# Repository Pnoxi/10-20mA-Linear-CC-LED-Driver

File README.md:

# 10-20mA-Linear-CC-LED-Driver

Documentation
--------------------

https://hackaday.io/project/164472-small-constant-current-linear-1020ma-driver

Donate
--------------------

Do you like my work? [Let me know about it and support my other projects!](https://www.patreon.com/pnoxi)

Or just drink beer on my honor :wink:

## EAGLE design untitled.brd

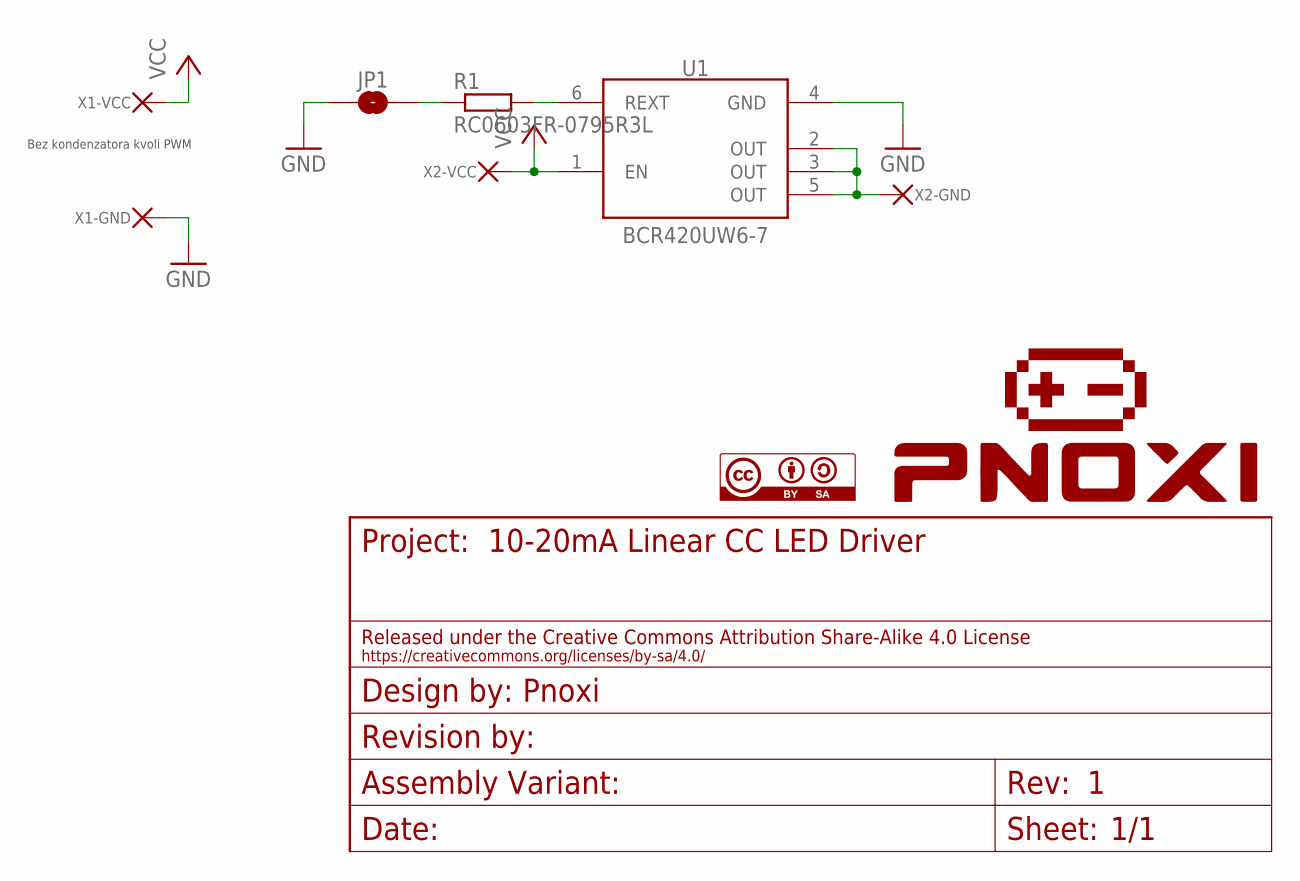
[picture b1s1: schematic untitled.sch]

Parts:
JP1: SMD-JUMPER-2-NO
R1: RC0603FR-0795R3L; 0603
U1: BCR420UW6-7; SOP95P250X110-6N-1_NO_THERMALS
X1, X2: SMD_PAD2; SMD_PAD_2

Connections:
GND: JP1.P$1 (1), U1.4 (GND), X1.GND, X1.GND1, X1.GND2, X1.GND3
unnamed: JP1.P$2 (2), R1.1
unnamed: R1.2, U1.6 (REXT)
unnamed: U1.2 (OUT), U1.3 (OUT), U1.5 (OUT), X2.GND, X2.GND1, X2.GND2, X2.GND3
VCC: U1.1 (EN), X1.VCC, X1.VCC1, X1.VCC2, X1.VCC3, X2.VCC, X2.VCC1, X2.VCC2, X2.VCC3

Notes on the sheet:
Bez kondenzatora kvoli PWM

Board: 2 copper layers, 5 parts (0 on the bottom side), 5 nets, no tracks yet.

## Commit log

2019-06-23 Added Design Files!

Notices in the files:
parts and their libraries:
Emsit-Frames: Released under the Creative Commons Attribution Share-Alike 4.0 License
Emsit-Frames: https://creativecommons.org/licenses/by-sa/4.0
